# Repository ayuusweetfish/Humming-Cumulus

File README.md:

# Humming Cumulus

[**概念展示动画 / Concept demo animation**](https://ayu.land/flow/rush/Cu_hum.mp4)

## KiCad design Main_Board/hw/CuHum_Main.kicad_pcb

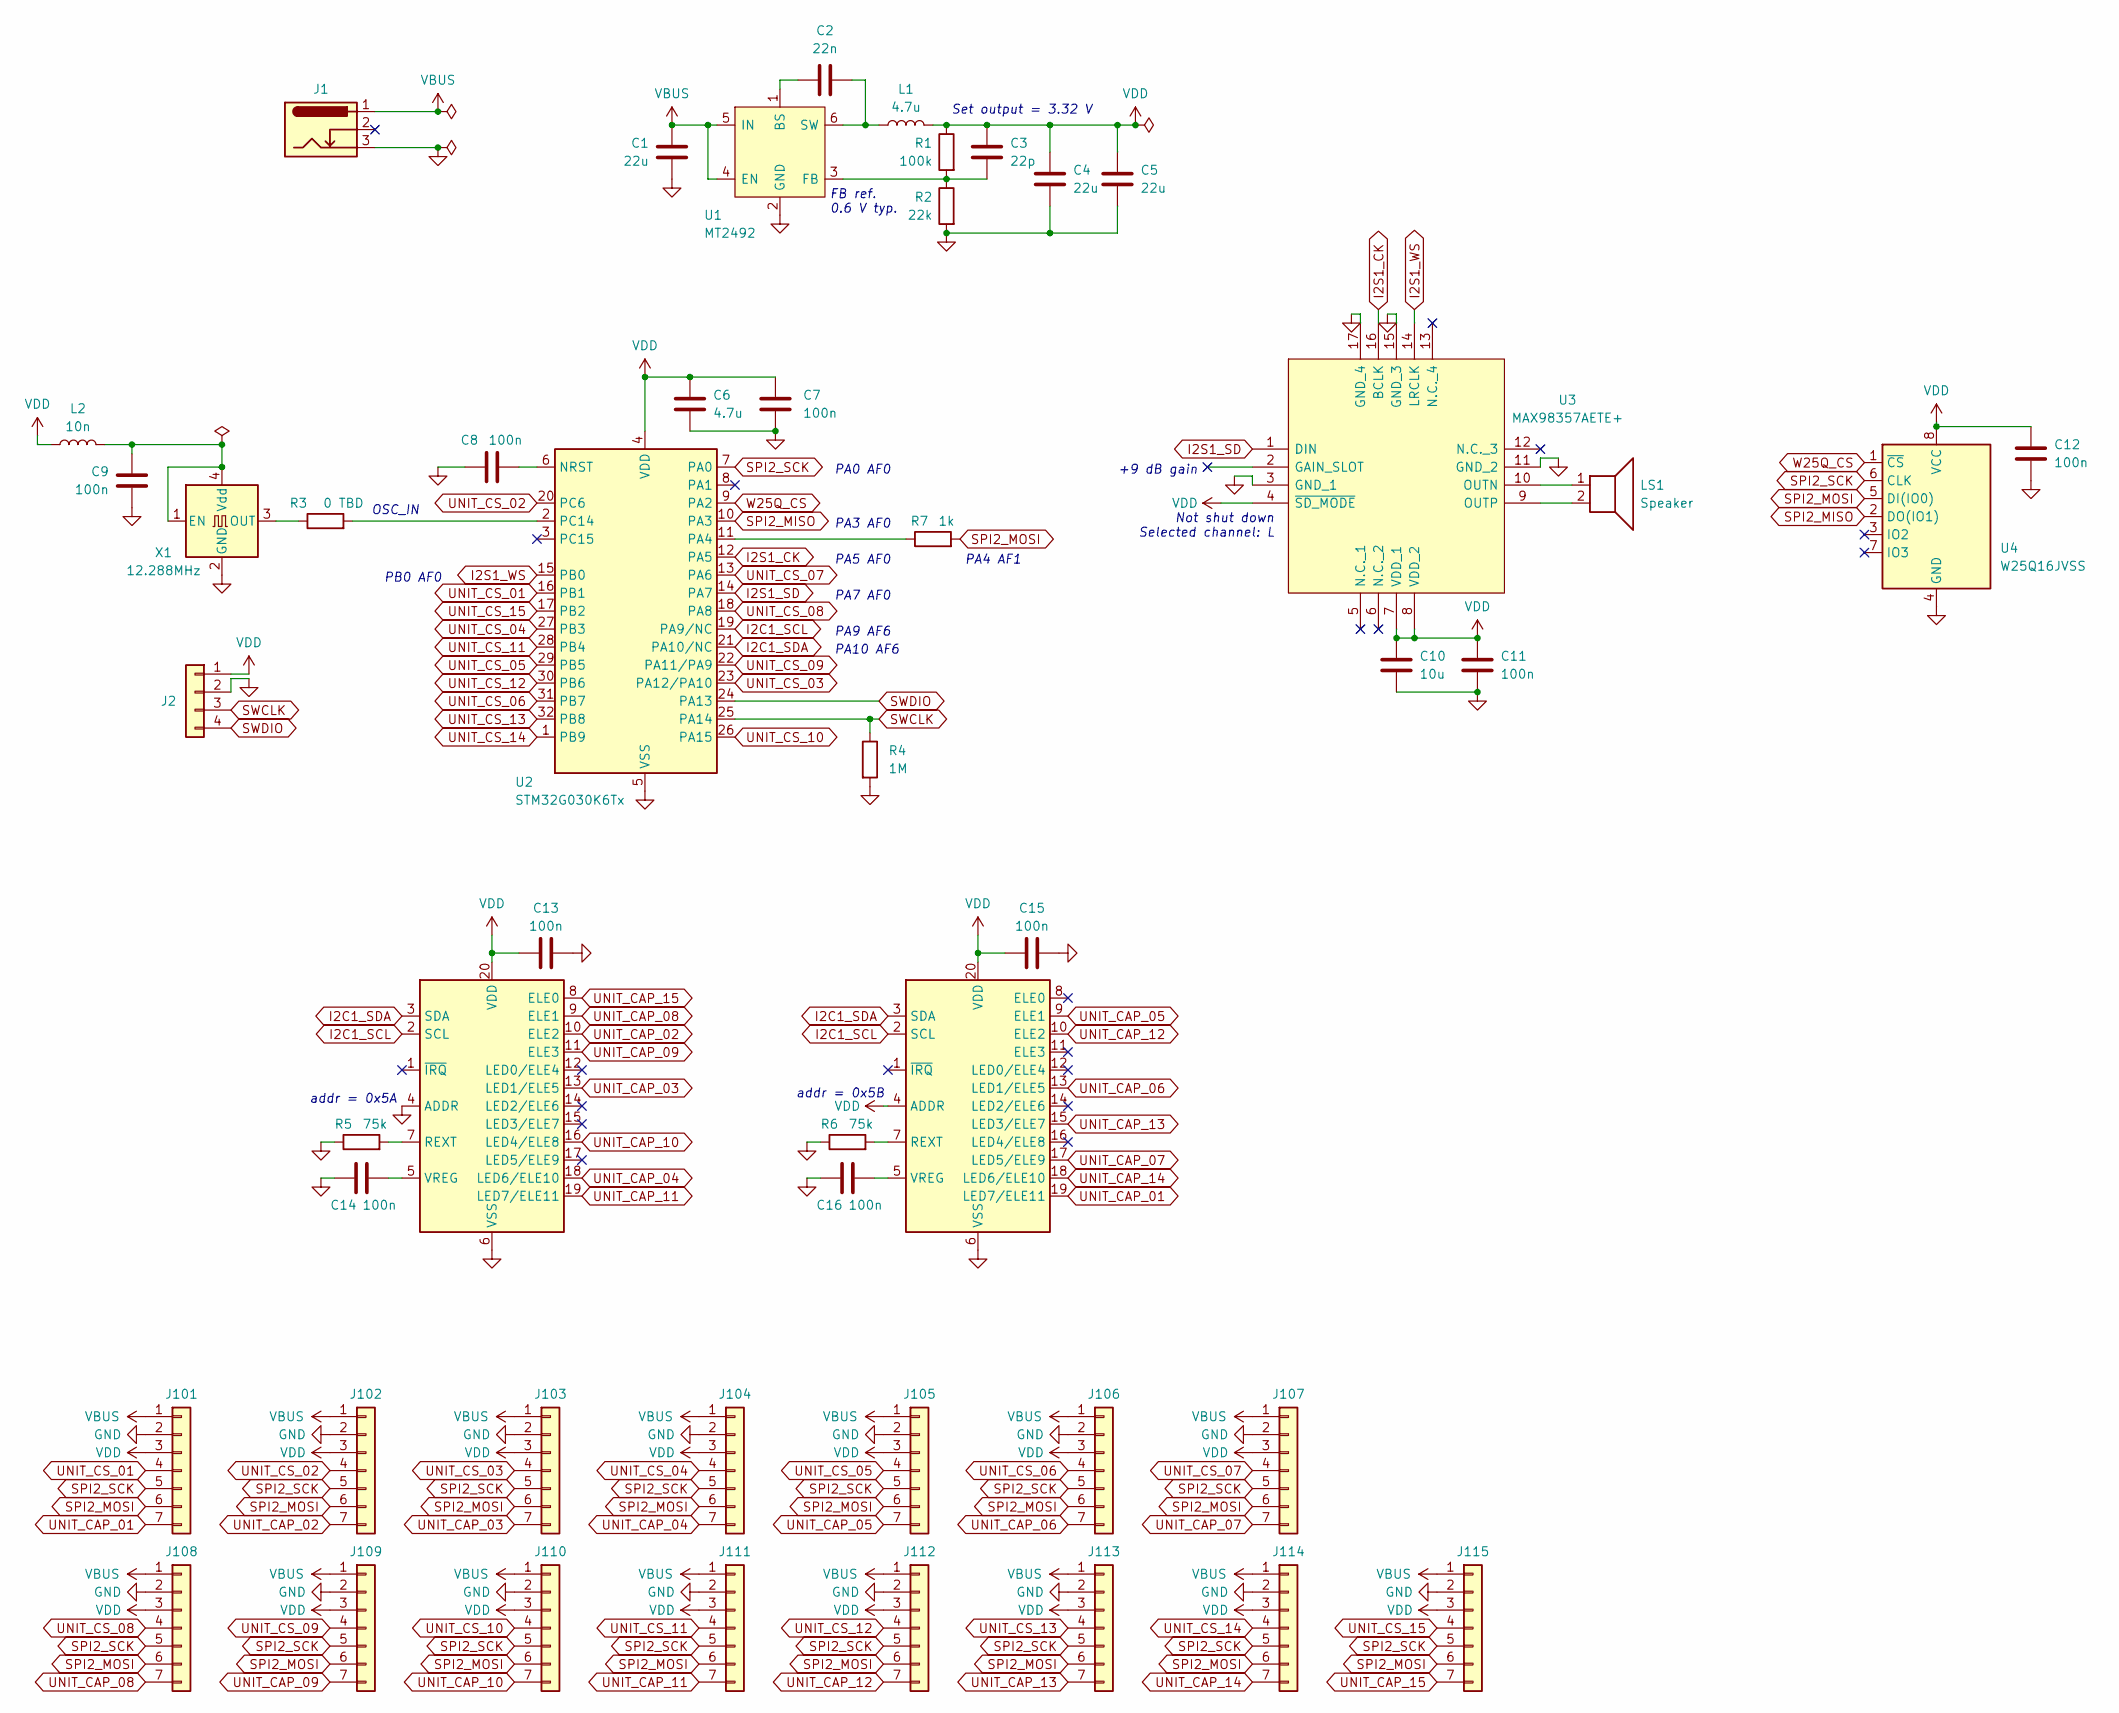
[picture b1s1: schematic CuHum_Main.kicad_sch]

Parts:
C1, C4, C5: 22u; C_0603_1608Metric
C2: 22n; C_0603_1608Metric
C3: 22p; C_0603_1608Metric
C6: 4.7u; C_0603_1608Metric
C7, C8, C11, C12, C13, C14, C15, C16: 100n; C_0603_1608Metric
C9: 100n; C_0402_1005Metric
C10: 10u; C_0603_1608Metric
J1: Barrel_Jack_Switch_Pin3Ring; BarrelJack_DC022
J2: Conn_01x04; TestPoints_1x04_P2.54
J101, J102, J103, J104, J105, J106, J107, J108, J109, J110, J111, J112, J113, J114, J115: Conn_01x07; Unit_1x07_P2.54
L1: 4.7u; L_Sunlord_MWSA1004S
L2: 10n; L_0402_1005Metric
LS1: Speaker; PinHeader_1x02_P2.54mm_Vertical
R1: 100k; R_0603_1608Metric
R2: 22k; R_0603_1608Metric
R3: 0 TBD; R_0603_1608Metric
R4: 1M; R_0603_1608Metric
R5, R6: 75k; R_0603_1608Metric
R7: 1k; R_0603_1608Metric
U1: MT2492; SOT-23-6; Manufacturer_Part_Number MT2492
U2: STM32G030K6Tx; LQFP-32_7x7mm_P0.8mm
U3: MAX98357AETE+; QFN-16-1EP_3x3mm_P0.5mm_EP1.45x1.45mm; Manufacturer_Part_Number MAX98357AETE+; Mouser Part Number 700-MAX98357AETE+
U4: W25Q16JVSS; SOIC-8_5.23x5.23mm_P1.27mm
U5, U6: MPR121QR2; UQFN-20_3x3mm_P0.4mm
X1: 12.288MHz; Oscillator_SMD_Abracon_ASE-4Pin_3.2x2.5mm

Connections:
GND: C1.2, C4.2, C5.2, C6.2, C7.2, C8.1, C9.2, C10.2, C11.2, C12.2, C13.2, C14.1, C15.2, C16.1, J1.3, J2.2, J101.2, J102.2, J103.2, J104.2, J105.2, J106.2, J107.2, J108.2, J109.2, J110.2, J111.2, J112.2, J113.2, J114.2, J115.2, R2.2, R4.2, R5.1, R6.1, U1.2 (GND), U2.5 (VSS), U3.3 (GND_1), U3.11 (GND_2), U3.15 (GND_3), U3.17 (GND_4), U4.4 (GND), U5.4 (ADDR), U5.6 (VSS), U6.6 (VSS), X1.2 (GND)
I2C1_SCL: U2.19 (PA9/NC), U5.2 (SCL), U6.2 (SCL)
I2C1_SDA: U2.21 (PA10/NC), U5.3 (SDA), U6.3 (SDA)
I2S1_CK: U2.12 (PA5), U3.16 (BCLK)
I2S1_SD: U2.14 (PA7), U3.1 (DIN)
I2S1_WS: U2.15 (PB0), U3.14 (LRCLK)
unnamed: C2.1, U1.1 (BS)
unnamed: C3.2, R1.2, R2.1, U1.3 (FB)
unnamed: C2.2, L1.1, U1.6 (SW)
unnamed: C8.2, U2.6 (NRST)
unnamed: R7.1, U2.11 (PA4)
unnamed: R3.2, U2.2 (PC14)
unnamed: LS1.1, U3.10 (OUTN)
unnamed: LS1.2, U3.9 (OUTP)
unnamed: R5.2, U5.7 (REXT)
unnamed: C14.2, U5.5 (VREG)
unnamed: R6.2, U6.7 (REXT)
unnamed: C16.2, U6.5 (VREG)
unnamed: C9.1, L2.2, X1.1 (EN), X1.4 (Vdd)
unnamed: R3.1, X1.3 (OUT)
SPI2_MISO: U2.10 (PA3), U4.2 (DO(IO1))
SPI2_MOSI: J101.6, J102.6, J103.6, J104.6, J105.6, J106.6, J107.6, J108.6, J109.6, J110.6, J111.6, J112.6, J113.6, J114.6, J115.6, R7.2, U4.5 (DI(IO0))
SPI2_SCK: J101.5, J102.5, J103.5, J104.5, J105.5, J106.5, J107.5, J108.5, J109.5, J110.5, J111.5, J112.5, J113.5, J114.5, J115.5, U2.7 (PA0), U4.6 (CLK)
SWCLK: J2.3, R4.1, U2.25 (PA14)
SWDIO: J2.4, U2.24 (PA13)
UNIT_CAP_01: J101.7, U6.19 (LED7/ELE11)
UNIT_CAP_02: J102.7, U5.10 (ELE2)
UNIT_CAP_03: J103.7, U5.13 (LED1/ELE5)
UNIT_CAP_04: J104.7, U5.18 (LED6/ELE10)
UNIT_CAP_05: J105.7, U6.9 (ELE1)
UNIT_CAP_06: J106.7, U6.13 (LED1/ELE5)
UNIT_CAP_07: J107.7, U6.17 (LED5/ELE9)
UNIT_CAP_08: J108.7, U5.9 (ELE1)
UNIT_CAP_09: J109.7, U5.11 (ELE3)
UNIT_CAP_10: J110.7, U5.16 (LED4/ELE8)
UNIT_CAP_11: J111.7, U5.19 (LED7/ELE11)
UNIT_CAP_12: J112.7, U6.10 (ELE2)
UNIT_CAP_13: J113.7, U6.15 (LED3/ELE7)
UNIT_CAP_14: J114.7, U6.18 (LED6/ELE10)
UNIT_CAP_15: J115.7, U5.8 (ELE0)
UNIT_CS_01: J101.4, U2.16 (PB1)
UNIT_CS_02: J102.4, U2.20 (PC6)
UNIT_CS_03: J103.4, U2.23 (PA12/PA10)
UNIT_CS_04: J104.4, U2.27 (PB3)
UNIT_CS_05: J105.4, U2.29 (PB5)
UNIT_CS_06: J106.4, U2.31 (PB7)
UNIT_CS_07: J107.4, U2.13 (PA6)
UNIT_CS_08: J108.4, U2.18 (PA8)
UNIT_CS_09: J109.4, U2.22 (PA11/PA9)
UNIT_CS_10: J110.4, U2.26 (PA15)
UNIT_CS_11: J111.4, U2.28 (PB4)
UNIT_CS_12: J112.4, U2.30 (PB6)
UNIT_CS_13: J113.4, U2.32 (PB8)
UNIT_CS_14: J114.4, U2.1 (PB9)
UNIT_CS_15: J115.4, U2.17 (PB2)
VBUS: C1.1, J1.1, J101.1, J102.1, J103.1, J104.1, J105.1, J106.1, J107.1, J108.1, J109.1, J110.1, J111.1, J112.1, J113.1, J114.1, J115.1, U1.4 (EN), U1.5 (IN)
VDD: C3.1, C4.1, C5.1, C6.1, C7.1, C10.1, C11.1, C12.1, C13.1, C15.1, J2.1, J101.3, J102.3, J103.3, J104.3, J105.3, J106.3, J107.3, J108.3, J109.3, J110.3, J111.3, J112.3, J113.3, J114.3, J115.3, L1.2, L2.1, R1.1, U2.4 (VDD), U3.4 (~SD_MODE), U3.7 (VDD_1), U3.8 (VDD_2), U4.8 (VCC), U5.20 (VDD), U6.4 (ADDR), U6.20 (VDD)
W25Q_CS: U2.9 (PA2), U4.1 (~CS)

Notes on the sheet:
PA9 AF6
PA0 AF0
OSC_IN
Set output = 3.32 V
FB ref. 0.6 V typ.
PA5 AF0
addr = 0x5B
PB0 AF0
PA10 AF6
addr = 0x5A
+9 dB gain
PA7 AF0
Not shut down Selected channel: L
PA3 AF0
PA4 AF1

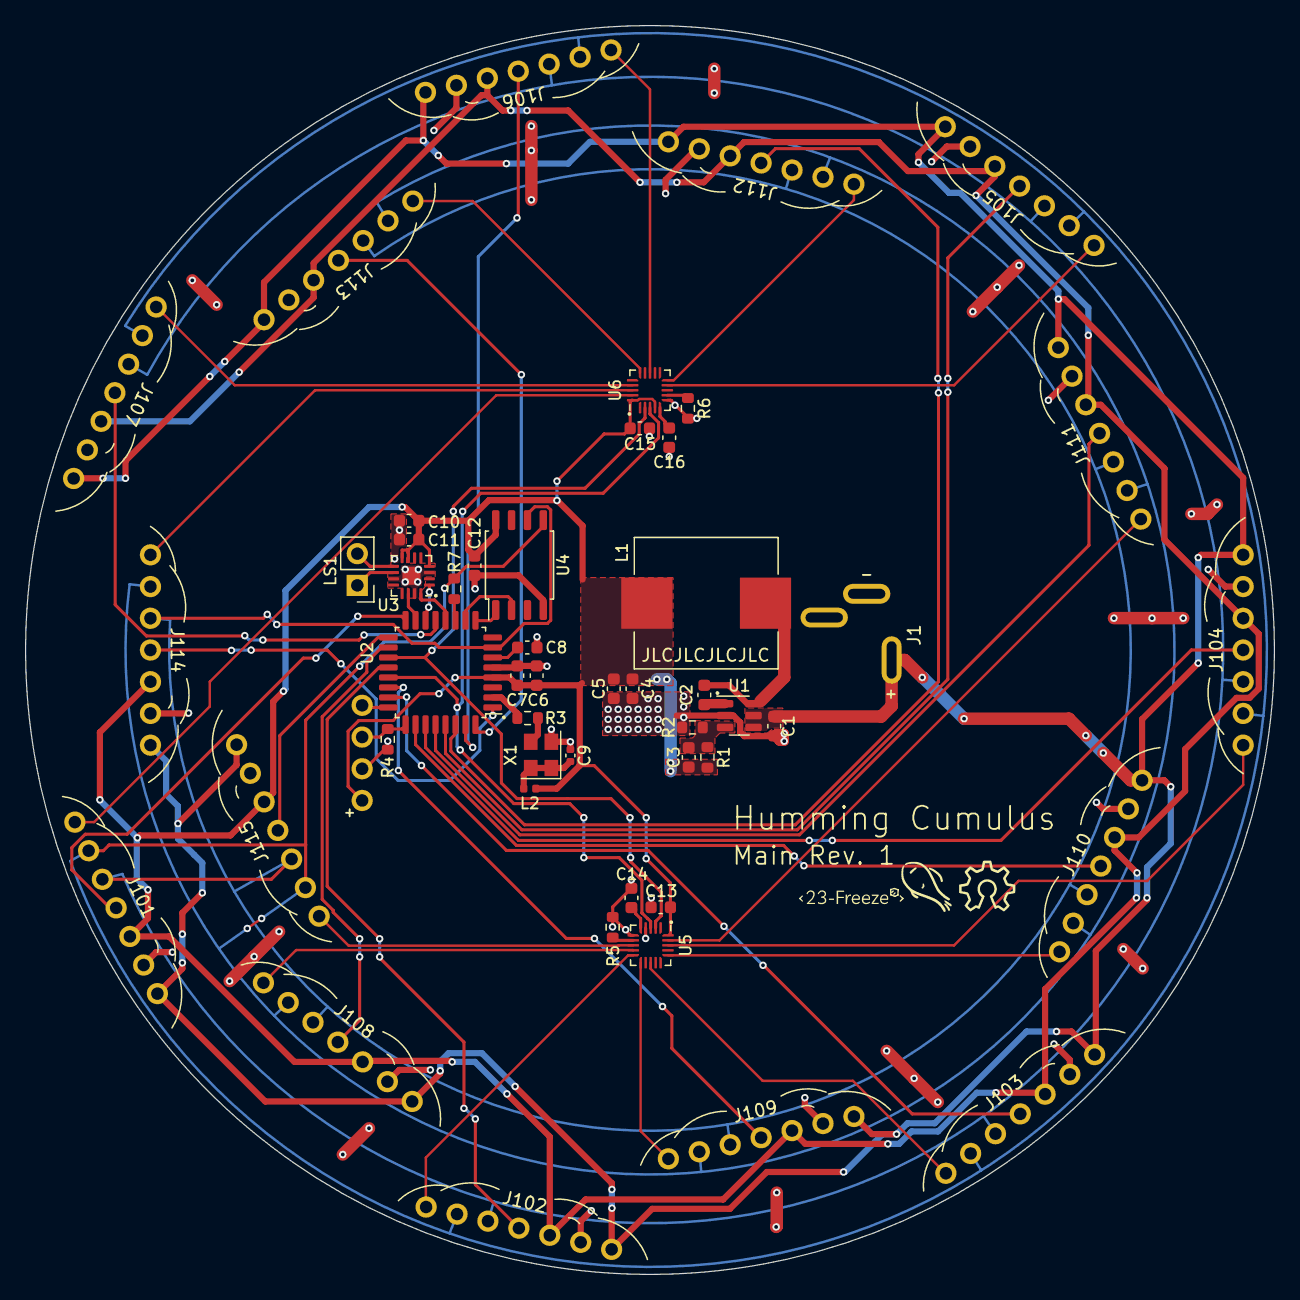
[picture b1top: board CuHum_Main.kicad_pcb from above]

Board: 2 copper layers, 100.0 x 100.0 mm, 50 parts (0 on the bottom side), 58 nets.

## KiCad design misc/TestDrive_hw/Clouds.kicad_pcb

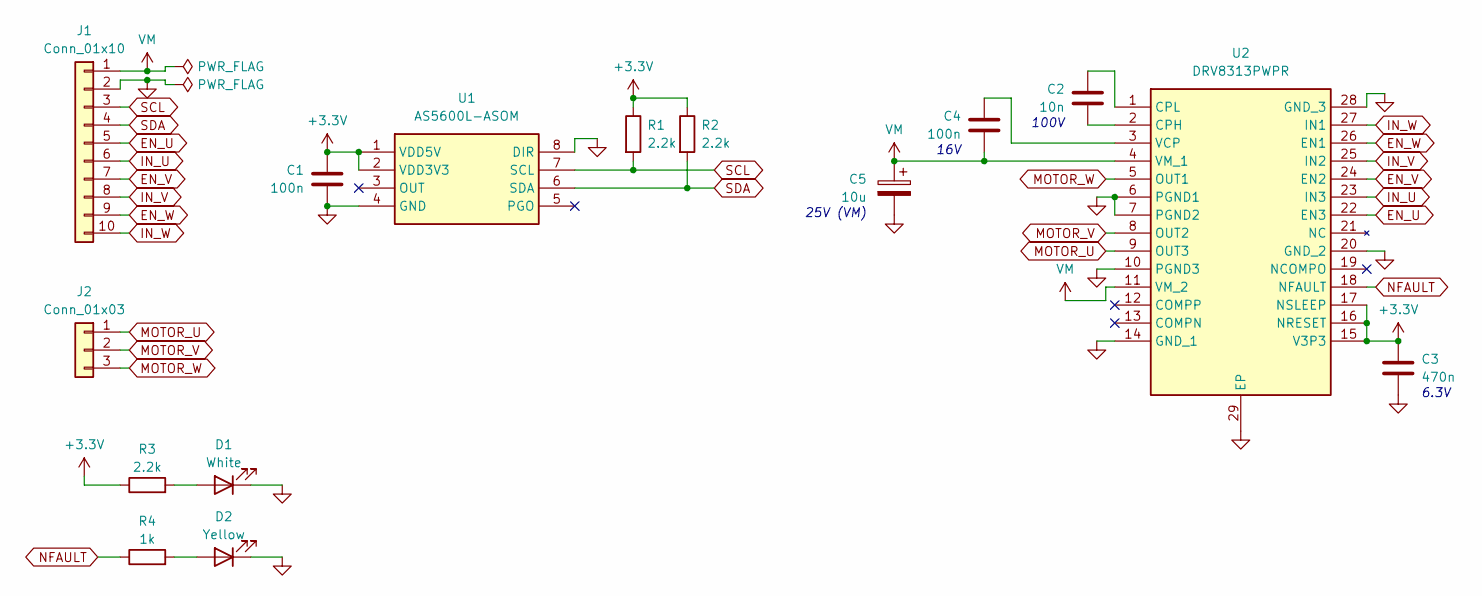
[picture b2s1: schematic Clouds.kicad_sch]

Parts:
C1, C4: 100n; C_0603_1608Metric
C2: 10n; C_0603_1608Metric
C3: 470n; C_0603_1608Metric
C5: 10u; CP_Elec_5x3.9
D1: White; LED_0805_2012Metric
D2: Yellow; LED_0805_2012Metric
J1: Conn_01x10; PinHeader_1x10_P2.54mm_Vertical
J2: Conn_01x03; PinHeader_1x03_P2.54mm_Vertical
R1, R2, R3: 2.2k; R_0603_1608Metric
R4: 1k; R_0603_1608Metric
U1: AS5600L-ASOM; SOIC127P600X175-8N; Manufacturer_Part_Number AS5600L-ASOM; Mouser Part Number 985-AS5600L-ASOM
U2: DRV8313PWPR; SOP65P640X120-29N; Manufacturer_Part_Number DRV8313PWPR; Mouser Part Number 595-DRV8313PWPR

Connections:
+3.3V: C1.1, C3.1, R1.1, R2.1, R3.1, U1.1 (VDD5V), U1.2 (VDD3V3), U2.15 (V3P3), U2.16 (NRESET), U2.17 (NSLEEP)
EN_U: J1.5, U2.22 (EN3)
EN_V: J1.7, U2.24 (EN2)
EN_W: J1.9, U2.26 (EN1)
GND: C1.2, C3.2, C5.2, D1.1 (K), D2.1 (K), J1.2, U1.4 (GND), U1.8 (DIR), U2.6 (PGND1), U2.7 (PGND2), U2.10 (PGND3), U2.14 (GND_1), U2.20 (GND_2), U2.28 (GND_3), U2.29 (EP)
IN_U: J1.6, U2.23 (IN3)
IN_V: J1.8, U2.25 (IN2)
IN_W: J1.10, U2.27 (IN1)
MOTOR_U: J2.1, U2.9 (OUT3)
MOTOR_V: J2.2, U2.8 (OUT2)
MOTOR_W: J2.3, U2.5 (OUT1)
NFAULT: R4.1, U2.18 (NFAULT)
unnamed: D1.2 (A), R3.2
unnamed: D2.2 (A), R4.2
unnamed: C2.2, U2.2 (CPH)
unnamed: C2.1, U2.1 (CPL)
unnamed: C4.1, U2.3 (VCP)
SCL: J1.3, R1.2, U1.7 (SCL)
SDA: J1.4, R2.2, U1.6 (SDA)
VM: C4.2, C5.1, J1.1, U2.4 (VM_1), U2.11 (VM_2)

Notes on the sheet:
25V (VM)
16V
100V
6.3V

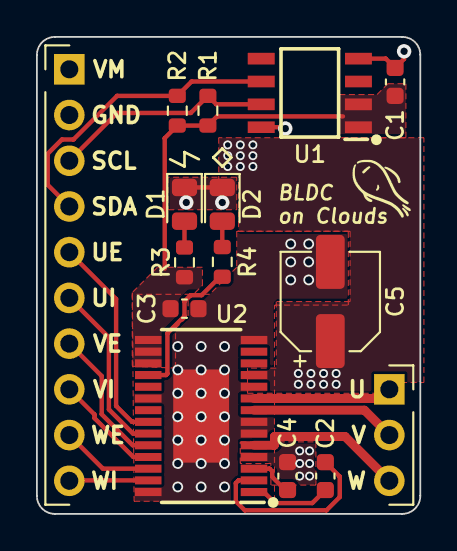
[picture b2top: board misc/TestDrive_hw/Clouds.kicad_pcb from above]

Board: 2 copper layers, 21.3 x 26.5 mm, 15 parts (0 on the bottom side), 20 nets.

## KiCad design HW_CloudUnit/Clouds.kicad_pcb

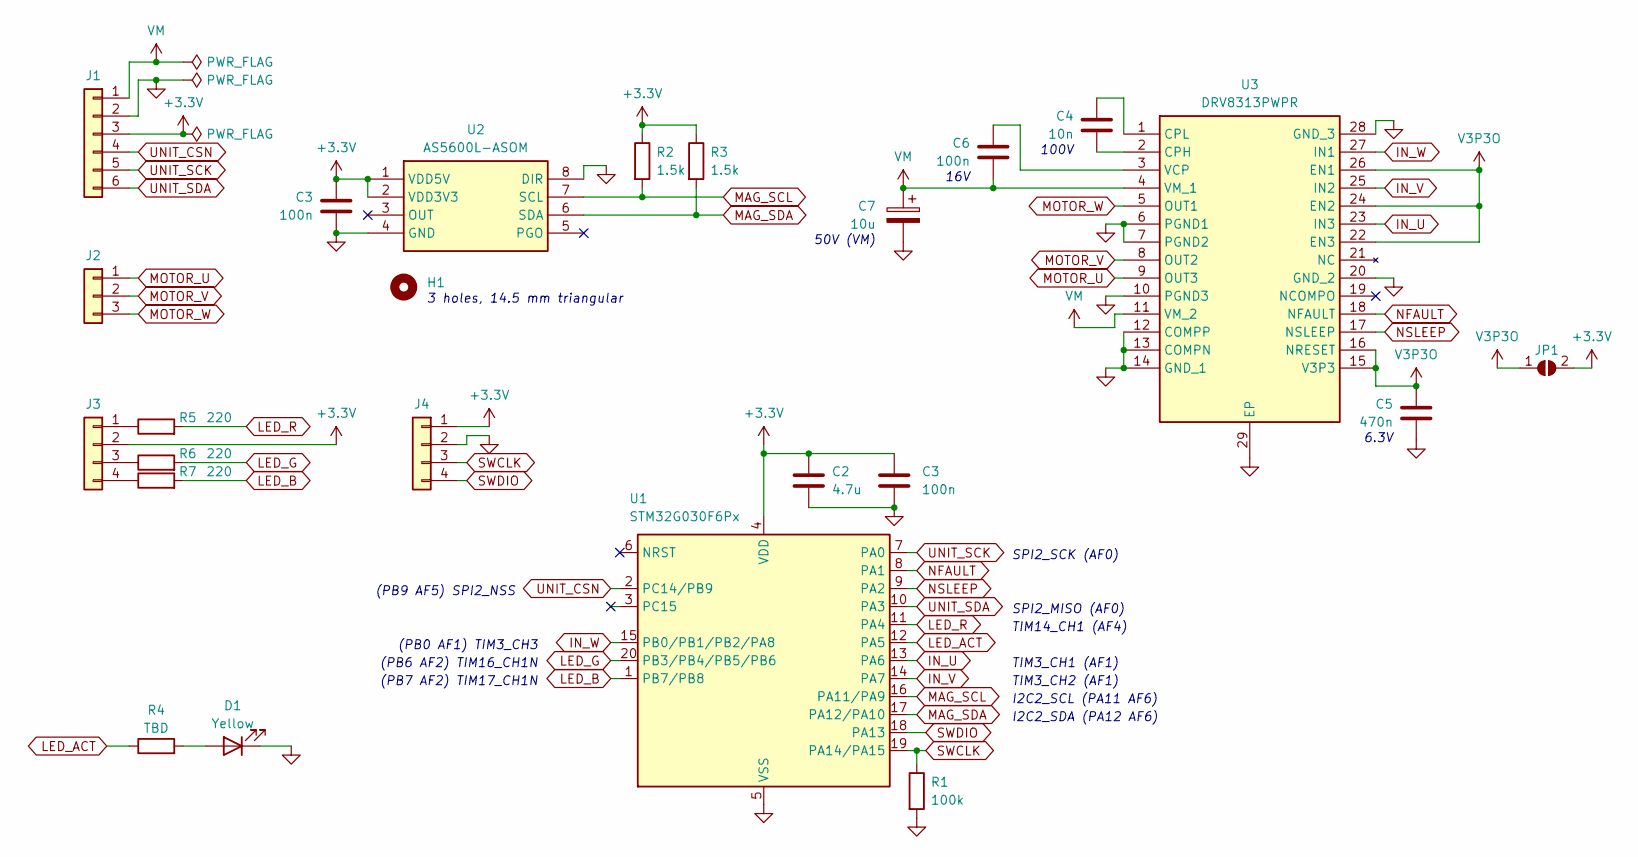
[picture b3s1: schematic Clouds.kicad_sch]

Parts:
C2: 4.7u; C_0603_1608Metric
C3, C6: 100n; C_0603_1608Metric
C4: 10n; C_0603_1608Metric
C5: 470n; C_0805_2012Metric
C7: 10u; CP_Elec_5x3.9
D1: Yellow; LED_0603_1608Metric
H1: MountingHole; MountingHoles_M3_Tri14.5
J1: Conn_01x06; PinHeader_1x06_P2.54mm_Vertical
J2: Conn_01x03; PinHeader_1x03_P2.54mm_Vertical
J3: Conn_01x04; PinHeader_1x04_P2.00mm_Vertical
J4: Conn_01x04; TestPoints_1x04_P2.0
JP1: SolderJumper_2_Open; SolderJumper-2_P1.3mm_Open_RoundedPad1.0x1.5mm
R1: 100k; R_0603_1608Metric
R2, R3: 1.5k; R_0603_1608Metric
R4: TBD; R_0603_1608Metric
R5, R6, R7: 220; R_0603_1608Metric
U1: STM32G030F6Px; TSSOP-20_4.4x6.5mm_P0.65mm
U2: AS5600L-ASOM; SOIC127P600X175-8N; Manufacturer_Part_Number AS5600L-ASOM; Mouser Part Number 985-AS5600L-ASOM
U3: DRV8313PWPR; SOP65P640X120-29N; Manufacturer_Part_Number DRV8313PWPR; Mouser Part Number 595-DRV8313PWPR

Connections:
+3.3V: C2.1, C3.1, J1.3, J3.2, J4.1, JP1.2 (B), R2.1, R3.1, U1.4 (VDD), U2.1 (VDD5V), U2.2 (VDD3V3); also elsewhere on the board
GND: C2.2, C3.2, C5.2, C7.2, D1.1 (K), J1.2, J4.2, R1.2, U1.5 (VSS), U2.4 (GND), U2.8 (DIR), U3.6 (PGND1), U3.7 (PGND2), U3.10 (PGND3), U3.12 (COMPP), U3.13 (COMPN), U3.14 (GND_1), U3.20 (GND_2), U3.28 (GND_3), U3.29 (EP); also elsewhere on the board
IN_U: U1.13 (PA6), U3.23 (IN3)
IN_V: U1.14 (PA7), U3.25 (IN2)
IN_W: U1.15 (PB0/PB1/PB2/PA8), U3.27 (IN1)
LED_ACT: R4.1, U1.12 (PA5)
LED_B: R7.2, U1.1 (PB7/PB8)
LED_G: R6.2, U1.20 (PB3/PB4/PB5/PB6)
LED_R: R5.2, U1.11 (PA4)
MAG_SCL: R2.2, U1.16 (PA11/PA9), U2.7 (SCL)
MAG_SDA: R3.2, U1.17 (PA12/PA10), U2.6 (SDA)
MOTOR_U: J2.1, U3.9 (OUT3)
MOTOR_V: J2.2, U3.8 (OUT2)
MOTOR_W: J2.3, U3.5 (OUT1)
NFAULT: U1.8 (PA1), U3.18 (NFAULT)
NSLEEP: U1.9 (PA2), U3.17 (NSLEEP)
unnamed: D1.2 (A), R4.2
unnamed: J3.1, R5.1
unnamed: J3.3, R6.1
unnamed: J3.4, R7.1
unnamed: C4.2, U3.2 (CPH)
unnamed: C4.1, U3.1 (CPL)
unnamed: C6.1, U3.3 (VCP)
SWCLK: J4.3, R1.1, U1.19 (PA14/PA15)
SWDIO: J4.4, U1.18 (PA13)
UNIT_CSN: J1.4, U1.2 (PC14/PB9)
UNIT_SCK: J1.5, U1.7 (PA0)
UNIT_SDA: J1.6, U1.10 (PA3)
V3P3O: C5.1, JP1.1 (A), U3.15 (V3P3), U3.16 (NRESET), U3.22 (EN3), U3.24 (EN2), U3.26 (EN1)
VM: C6.2, C7.1, J1.1, U3.4 (VM_1), U3.11 (VM_2)

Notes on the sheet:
I2C2_SCL (PA11 AF6)
I2C2_SDA (PA12 AF6)
(PB0 AF1) TIM3_CH3
SPI2_SCK (AF0)
(PB7 AF2) TIM17_CH1N
50V (VM)
16V
(PB9 AF5) SPI2_NSS
(PB6 AF2) TIM16_CH1N
100V
TIM3_CH1 (AF1)
TIM3_CH2 (AF1)
TIM14_CH1 (AF4)
6.3V
SPI2_MISO (AF0)
3 holes, 14.5 mm triangular

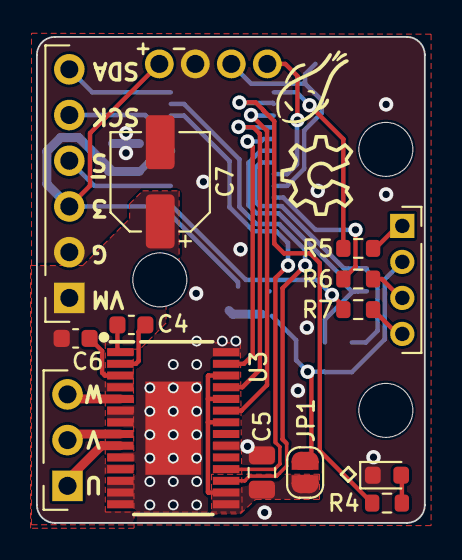
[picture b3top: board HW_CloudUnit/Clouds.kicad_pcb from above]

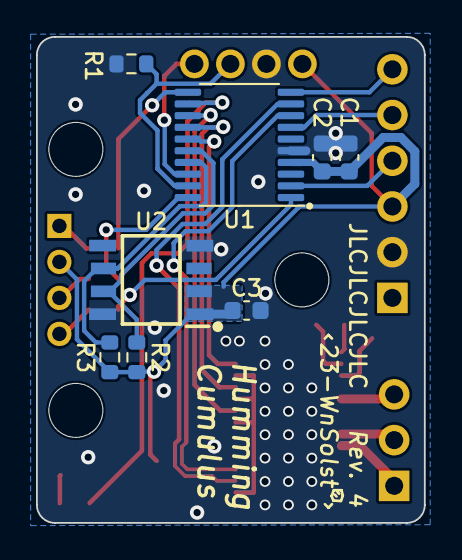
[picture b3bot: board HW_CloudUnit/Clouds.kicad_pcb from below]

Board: 2 copper layers, 21.6 x 27.0 mm, 24 parts (8 on the bottom side), 30 nets.

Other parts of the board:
C1: 4.7u; C_0603_1608Metric

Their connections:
+3.3V: C1.1; also elsewhere on the board
GND: C1.2; also elsewhere on the board

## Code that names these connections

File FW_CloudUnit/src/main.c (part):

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  HAL_GPIO_Init(LED_IND_ACT_PORT, &gpio_init);
  HAL_GPIO_WritePin(LED_IND_ACT_PORT, LED_IND_ACT_PIN, GPIO_PIN_SET);

  // SWD (PA13, PA14)
  gpio_init.Pin = GPIO_PIN_13 | GPIO_PIN_14;
  gpio_init.Mode = GPIO_MODE_AF_PP; // Pass over control to AF peripheral
  gpio_init.Alternate = GPIO_AF0_SWJ;
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  HAL_TIM_PWM_ConfigChannel(&tim3, &tim3_ch1_oc_init, TIM_CHANNEL_3);
  HAL_TIM_PWM_Start(&tim3, TIM_CHANNEL_3);

  // Driver nFAULT and nSLEEP pins
  gpio_init.Pin = DRV_NFAULT_PIN;
  gpio_init.Mode = GPIO_MODE_INPUT;
  gpio_init.Pull = GPIO_PULLUP;
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
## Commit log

2023-11-30 Add ECAD libraries for IC components
2023-11-30 Finish schematics
2023-11-30 Revise schematic
2023-11-30 (WIP) PCB layout
2023-11-30 (WIP) Almost-complete layout
2023-11-30 Finish PCB design
2023-11-30 Prepare test drive board for fabrication
2023-12-01 Create new unit controller board
2023-12-01 (WIP) Layout of driver board
2023-12-01 (WIP) Try routing
2023-12-01 Finish driver board design
2023-12-01 Fix motor's wire order
2023-12-08 ✨ Start work on firmware, blinking
2023-12-08 Blinking RGB LED
2023-12-08 PWM test by fading LED
2023-12-08 Smooth fading colours
2023-12-08 Read values from magnetic encoder
2023-12-08 🌀 Fade & dim lights according to the magnet!
2023-12-11 Update boards with NPTH screw holes
2023-12-11 Add I2S audio test on development board
2023-12-11 Test externally-triggered timer
2023-12-11 Test timer synchronisation with serial clock signal
2023-12-12 (WIP) Output signals to the driver IC
2023-12-13 PWM to driver pins
2023-12-14 (WIP) Adjust PWM to driver pins
2023-12-14 Add README with images
2023-12-18 Correctly driving BLDC motor
2023-12-18 Rotate the motor back and forth
2023-12-20 Enable PLL, output PWM at higher frequency
2023-12-21 Update clouds unit PCB with new motor dimensions
2023-12-21 Further revise PCB design
2023-12-22 Revise PCB and submit for fabrication (Rev. 4)
2023-12-31 Upload FW onto updated HW; only read mag encoder
2024-01-01 Run testdrive firmware on updated hardware
2024-01-01 Add a mechanical part for elevation of the motor
2024-01-03 Update mechanical parts
2024-01-07 Revise mechanical parts for the pulley
2024-01-16 Test more rotations with breathing lights
2024-01-16 Optimise spindle dimensions
2024-01-16 Bring back encoder read-outs in firmware
2024-01-17 Signal on I2C errors
2024-01-18 Add motor chassis model
2024-01-18 Revise incorrect chassis model
2024-01-23 Revise cloud unit chassis part
2024-01-24 Revise chassis model again
2024-01-24 Reorganise directory structure
2024-01-24 Add schematic for the main board
2024-01-25 Finish main board layout
2024-01-26 2 revolutions instead of 3
2024-01-26 (WIP) Main board layout & routing
2024-01-26 Finish main board routing
2024-01-27 Finish main board design
2024-01-27 Revise mechanical parts, again
2024-02-03 Add link to concept demo animation
2024-02-14 Add paper template
2024-02-14 (WIP) Paper
2024-02-15 Paper submission
